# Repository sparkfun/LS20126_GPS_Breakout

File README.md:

**NOTE:** *This product has been retired from our catalog. If you are looking for more up-to-date info, please check out some of these resources to see how other users are still hacking and improving on this product.*
* *[SparkFun Forum](https://forum.sparkfun.com/)*
* *[Comments Here on GitHub](https://github.com/sparkfun/LS20126_GPS_Breakout/issues)*
* *[IRC Channel](https://www.sparkfun.com/news/263)*

LS20126 GPS Breakout
====================

[*SparkFun LS20126 GPS Breakout (BOB-10141)*](https://www.sparkfun.com/products/10141)

This pcb breaks out the [LS20126 GPS receiver](https://www.sparkfun.com/products/retired/9838) pins to standard 0.1" headers. 

Repository Contents
-------------------
* **/Hardware** - All Eagle design files (.brd, .sch)

License Information
-------------------
The hardware is released under [Creative Commons ShareAlike 4.0 International](https://creativecommons.org/licenses/by-sa/4.0/).

Distributed as-is; no warranty is given.

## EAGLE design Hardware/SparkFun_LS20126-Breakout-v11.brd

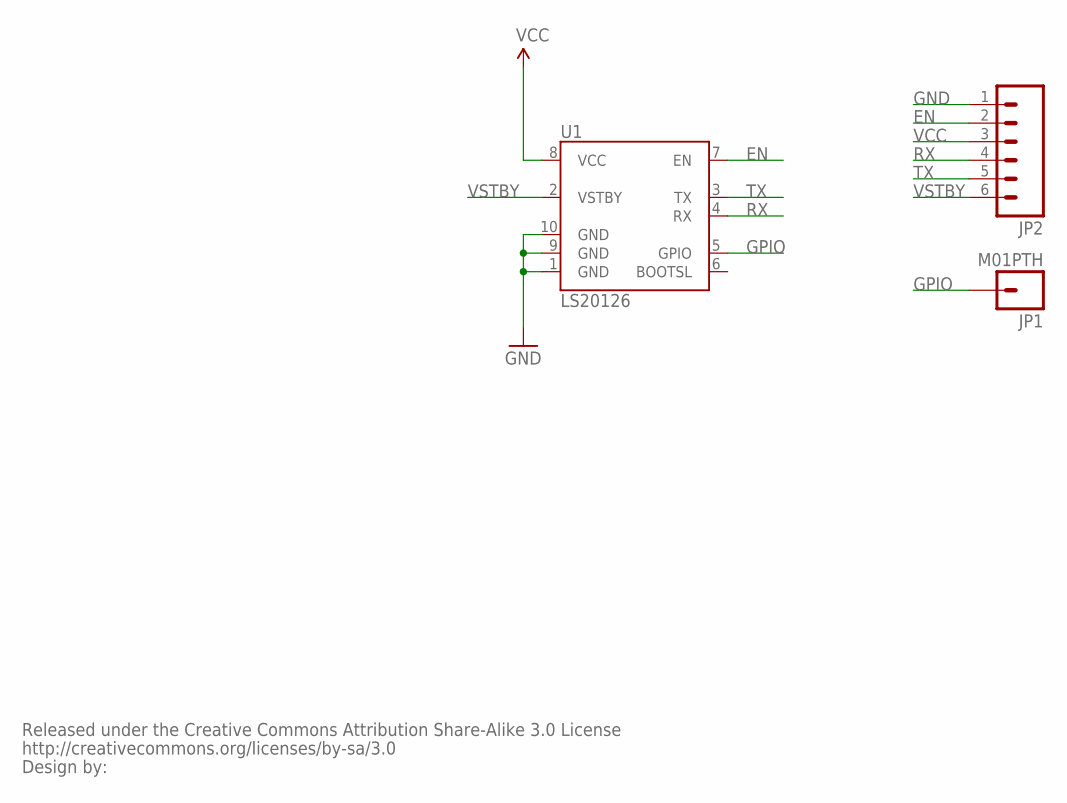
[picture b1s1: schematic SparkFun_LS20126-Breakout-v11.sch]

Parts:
JP1: M01PTH; 1X01
JP2: M06SIP; 1X06
U1: LS20126
U$1: CREATIVE_COMMONS

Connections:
EN: JP2.2, U1.7 (EN)
GND: JP2.1, U1.1 (GND), U1.9 (GND), U1.10 (GND)
GPIO: JP1.1, U1.5 (GPIO)
RX: JP2.4, U1.4 (RX)
TX: JP2.5, U1.3 (TX)
VCC: JP2.3, U1.8 (VCC)
VSTBY: JP2.6, U1.2 (VSTBY)

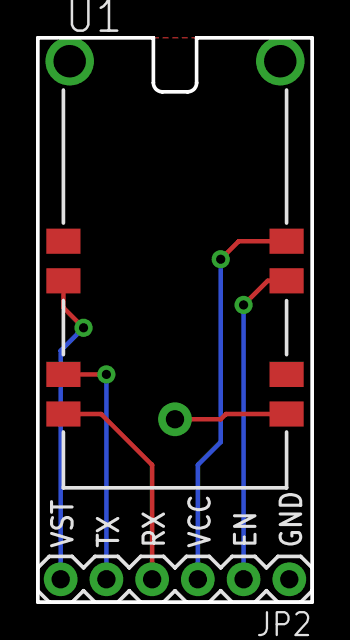
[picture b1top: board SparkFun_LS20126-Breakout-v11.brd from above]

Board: 2 copper layers, 15.2 x 31.4 mm, 4 parts (1 on the bottom side), 7 nets.

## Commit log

2015-01-06 Initial hardware commit

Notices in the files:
parts and their libraries:
SparkFun: Released under the Creative Commons Attribution Share-Alike 3.0 License
SparkFun: http://creativecommons.org/licenses/by-sa/3.0
